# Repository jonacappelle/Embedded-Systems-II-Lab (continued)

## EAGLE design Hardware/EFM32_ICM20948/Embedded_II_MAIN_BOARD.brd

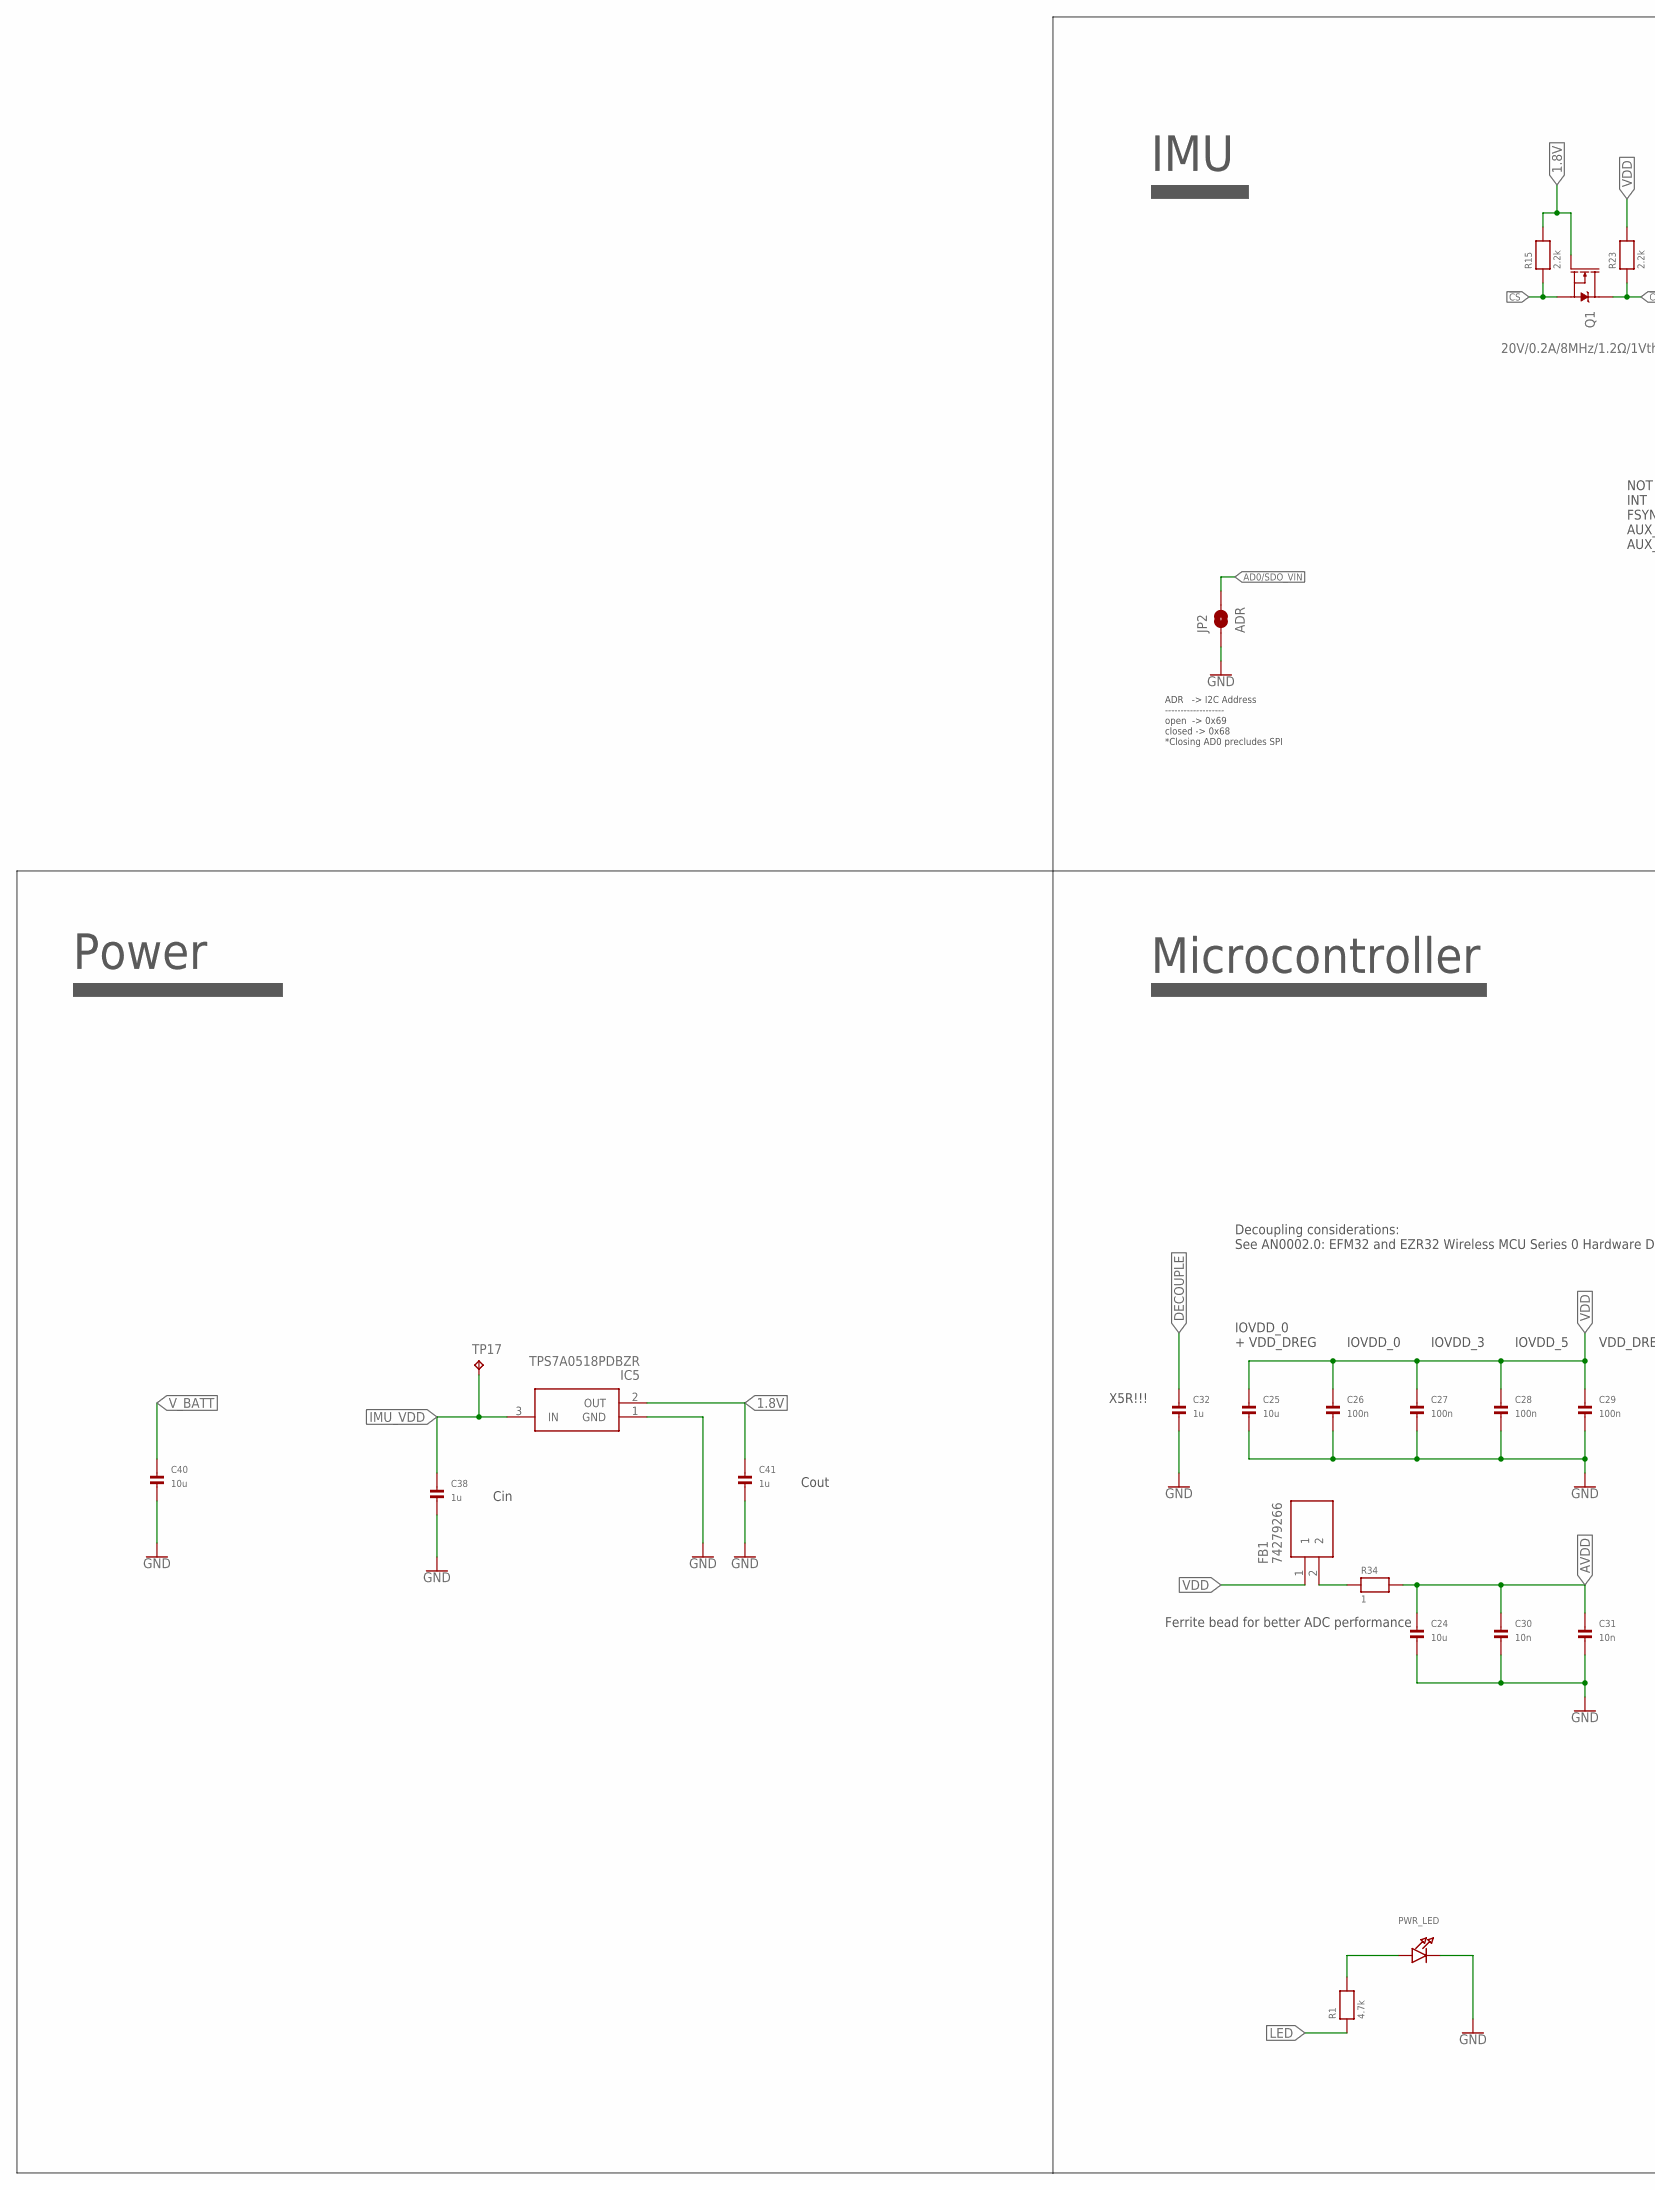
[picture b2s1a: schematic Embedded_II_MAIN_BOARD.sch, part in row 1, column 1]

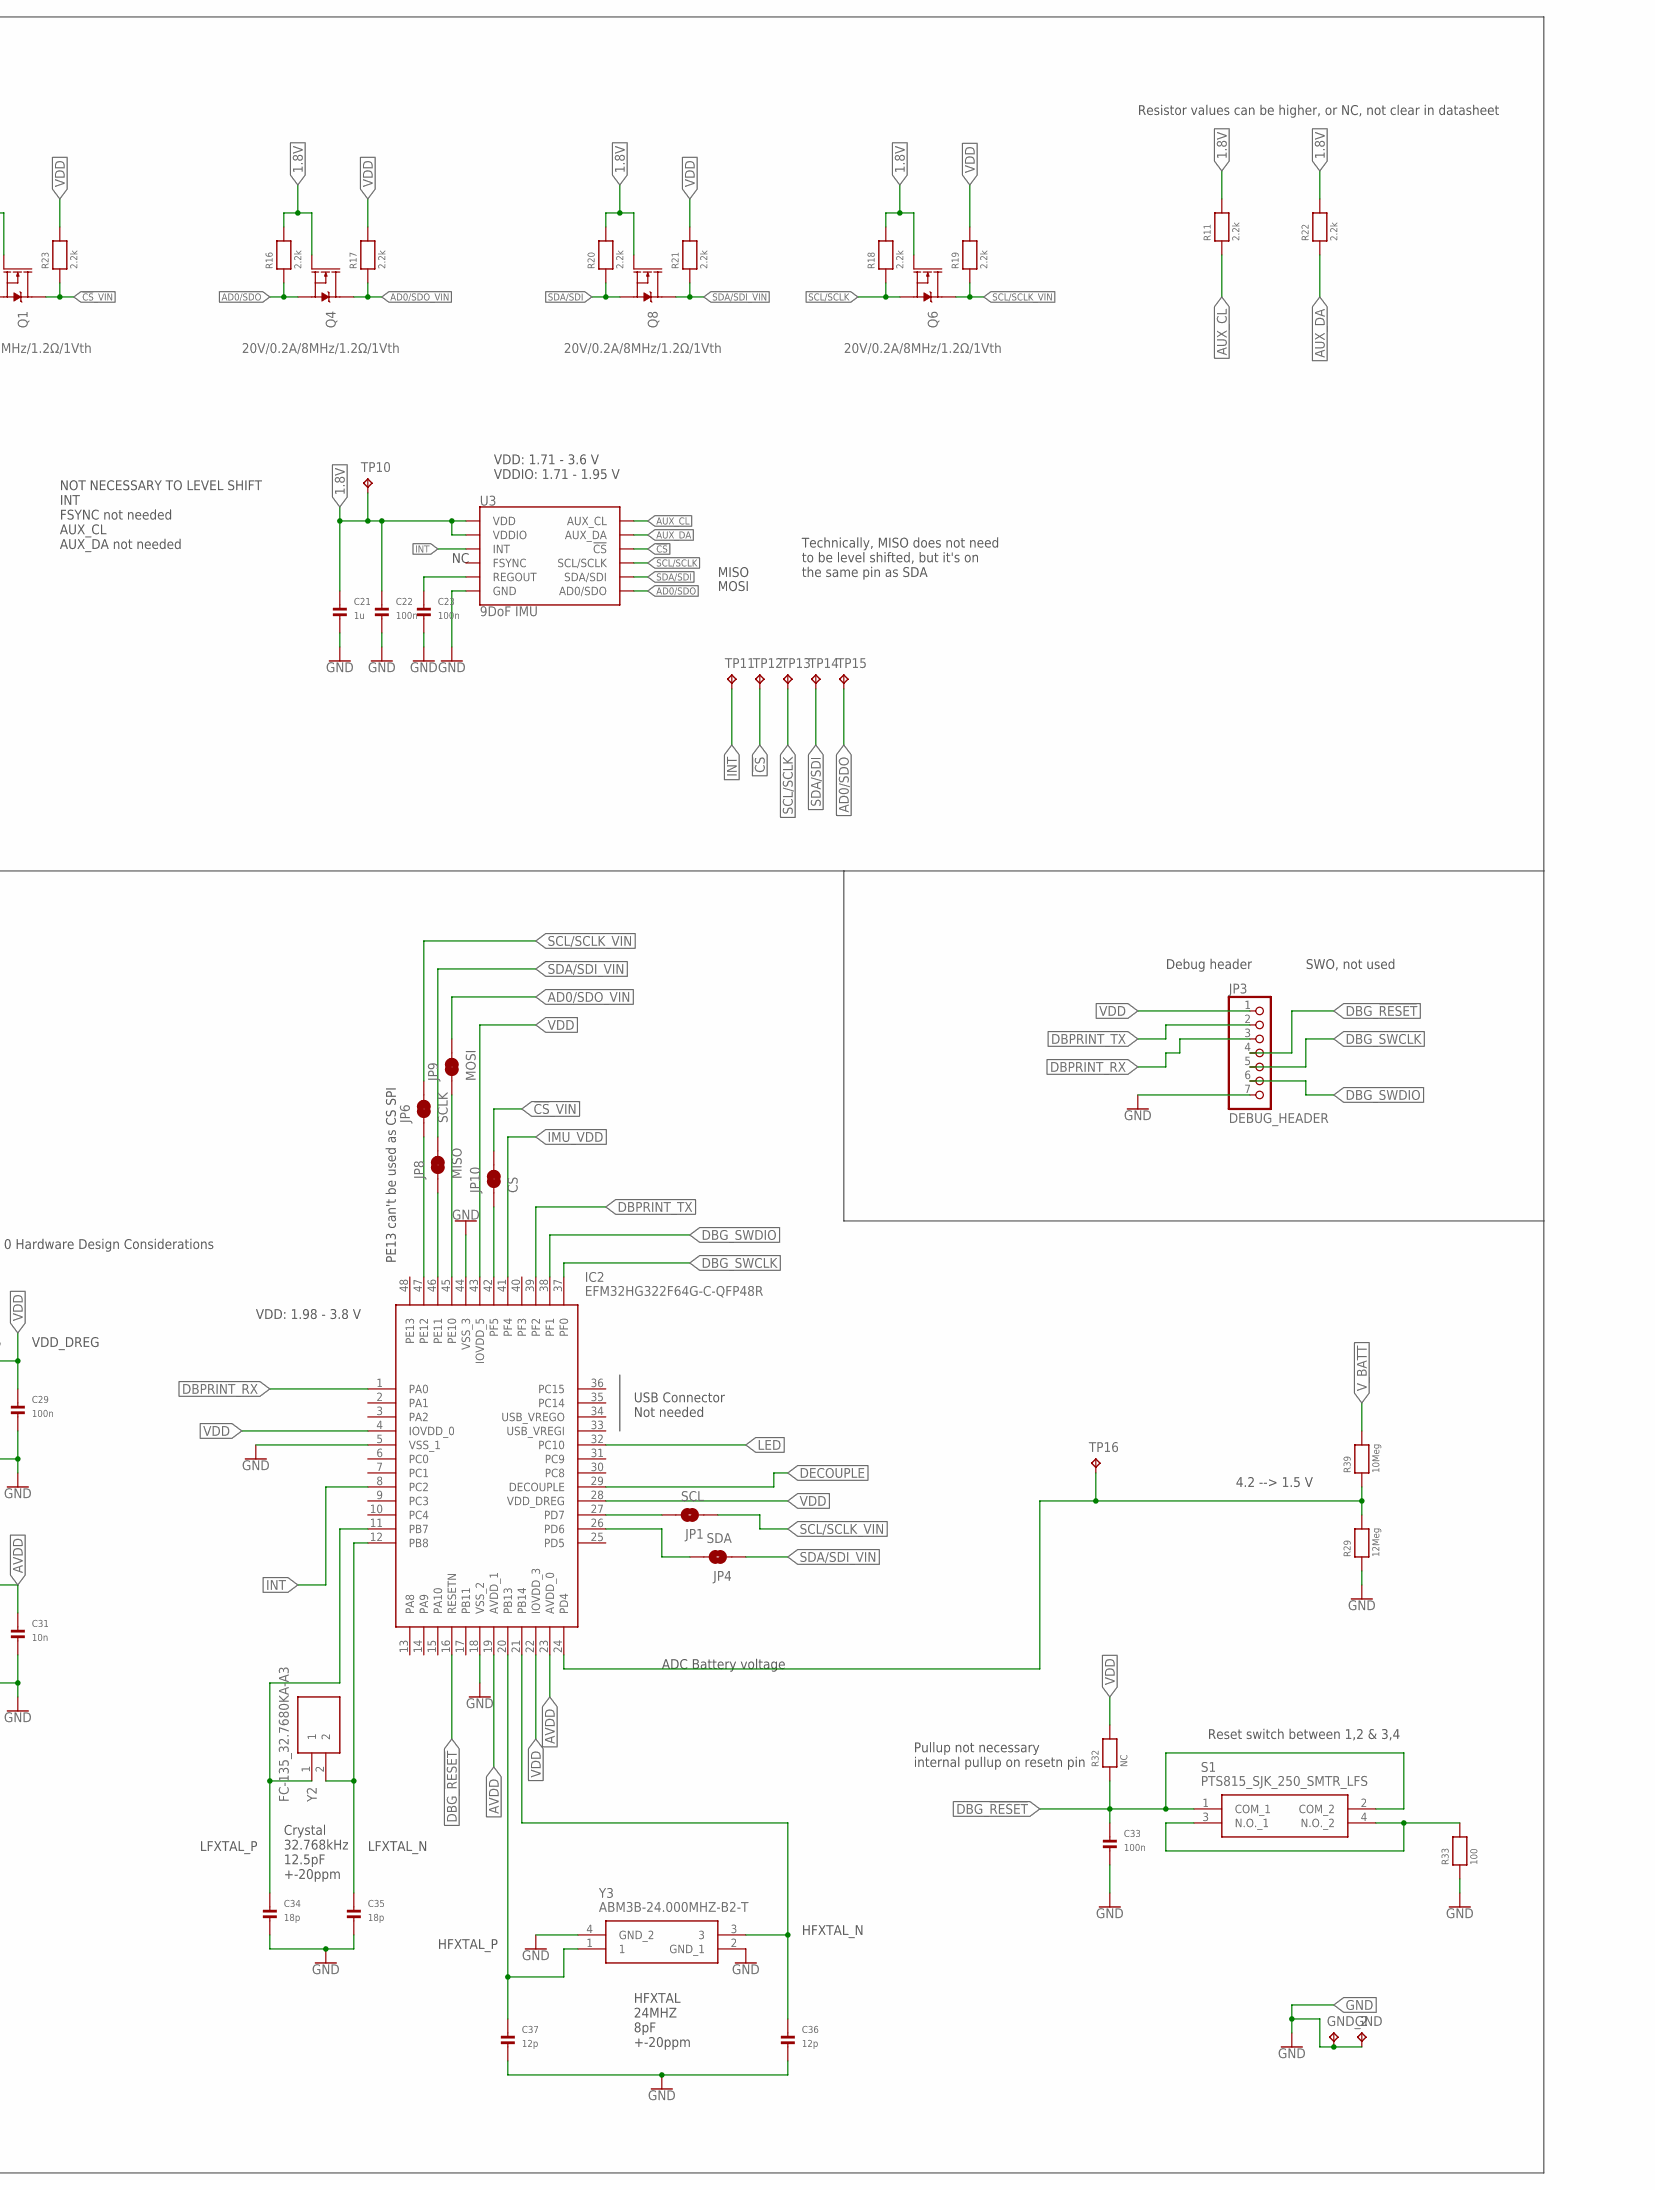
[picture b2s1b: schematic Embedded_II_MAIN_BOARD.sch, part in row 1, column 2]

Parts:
C21, C32, C38, C41: 1u; 0603
C22, C23, C26, C27, C28, C29, C33: 100n; 0603
C24, C25, C40: 10u; 0603
C30, C31: 10n; 0603
C34, C35: 18p; 0603
C36, C37: 12p; 0603
FB1: 74279266; BEADC1608X100N
GND: TPTP20SQ; TP20SQ
GND_2: TPTP20SQ; TP20SQ
IC2: EFM32HG322F64G-C-QFP48R; QFP50P900X900X120-48N
IC5: TPS7A0518PDBZR; SOT95P237X112-3N
JP1: SCL; SMT-JUMPER_2_NO_SILK
JP2: ADR; SMT-JUMPER_2_NO_SILK
JP3: DEBUG_HEADER; 1X07
JP4: SDA; SMT-JUMPER_2_NO_SILK
JP6: SCLK; SMT-JUMPER_2_NC_TRACE_SILK
JP8: MISO; SMT-JUMPER_2_NC_TRACE_SILK
JP9: MOSI; SMT-JUMPER_2_NC_TRACE_SILK
JP10: CS; SMT-JUMPER_2_NC_TRACE_SILK
PWR_LED: LED0805; CHIPLED_0805
Q1, Q4, Q6, Q8: 20V/0.2A/8MHz/1.2Ω/1Vth; SOT-416FL
R1: 4.7k; 0603
R11, R15, R16, R17, R18, R19, R20, R21, R22, R23: 2.2k; 0603
R29: 12Meg; 0603
R32: NC; 0603
R33: 100; 0603
R34: 1; 0603
R39: 10Meg; 0603
S1: PTS815_SJK_250_SMTR_LFS; PTS815SJK250SMTRLFS
TP10, TP11, TP12, TP13, TP14, TP15, TP16, TP17: TPTP10R; TP10R
U3: 9DoF IMU; SPARKFUN-SENSORS_QFN24-3X3
Y2: FC-135_32.7680KA-A3; FC135327680KAAG0
Y3: ABM3B-24.000MHZ-B2-T; ABM3B8000MHZ101UT

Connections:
1.8V: C21.1, C22.1, C41.1, IC5.2 (OUT), Q1.1 (G), Q4.1 (G), Q6.1 (G), Q8.1 (G), R11.2, R15.2, R16.2, R18.2, R20.2, R22.2, TP10.TP, U3.8 (VDDIO), U3.13 (VDD)
!CS: Q1.2 (S), R15.1, TP12.TP, U3.22 (!CS)
!CS!_VIN: JP10.2, Q1.3 (D), R23.1
AD0/SDO: Q4.2 (S), R16.1, TP15.TP, U3.9 (AD0/SDO)
AD0/SDO_VIN: JP2.2, JP9.2, Q4.3 (D), R17.1
AUX_CL: R11.1, U3.7 (AUX_CL)
AUX_DA: R22.1, U3.21 (AUX_DA)
AVDD: C24.1, C30.1, C31.1, IC2.19 (AVDD_1), IC2.23 (AVDD_0), R34.2
DBG_!RESET: C33.1, IC2.16 (RESETN), JP3.4, R32.1, S1.1 (COM_1), S1.2 (COM_2)
DBG_SWCLK: IC2.37 (PF0), JP3.5
DBG_SWDIO: IC2.38 (PF1), JP3.6
DBPRINT_RX: IC2.1 (PA0), JP3.3
DBPRINT_TX: IC2.39 (PF2), JP3.2
DECOUPLE: C32.1, IC2.29 (DECOUPLE)
GND: C21.2, C22.2, C23.2, C24.2, C25.2, C26.2, C27.2, C28.2, C29.2, C30.2, C31.2, C32.2, C33.2, C34.2, C35.2, C36.2, C37.2, C38.2, C40.2, C41.2, GND.TP, GND_2.TP, IC2.5 (VSS_1), IC2.18 (VSS_2), IC2.44 (VSS_3), IC5.1 (GND), JP2.1, JP3.7, PWR_LED.C, R29.1, R33.1, U3.18 (GND), U3.20 (GND), Y3.2 (GND_1), Y3.4 (GND_2)
IMU_VDD: C38.1, IC2.41 (PF4), IC5.3 (IN), TP17.TP
INT: IC2.8 (PC2), TP11.TP, U3.12 (INT)
LED: IC2.32 (PC10), R1.1
unnamed: IC2.27 (PD7), JP1.2
unnamed: PWR_LED.A, R1.2
unnamed: IC2.26 (PD6), JP4.2
unnamed: IC2.47 (PE12), JP6.1
unnamed: C35.1, IC2.12 (PB8), Y2.2
unnamed: C23.1, U3.10 (REGOUT)
unnamed: IC2.46 (PE11), JP8.1
unnamed: IC2.45 (PE10), JP9.1
unnamed: IC2.24 (PD4), R29.2, R39.1, TP16.TP
unnamed: C34.1, IC2.11 (PB7), Y2.1
unnamed: IC2.42 (PF5), JP10.1
unnamed: C37.1, IC2.20 (PB13), Y3.1
unnamed: C36.1, IC2.21 (PB14), Y3.3
unnamed: R33.2, S1.3 (N.O._1), S1.4 (N.O._2)
unnamed: FB1.2, R34.1
SCL/SCLK: Q6.2 (S), R18.1, TP13.TP, U3.23 (SCL/SCLK)
SCL/SCLK_VIN: JP1.1, JP6.2, Q6.3 (D), R19.1
SDA/SDI: Q8.2 (S), R20.1, TP14.TP, U3.24 (SDA/SDI)
SDA/SDI_VIN: JP4.1, JP8.2, Q8.3 (D), R21.1
VDD: C25.1, C26.1, C27.1, C28.1, C29.1, FB1.1, IC2.4 (IOVDD_0), IC2.22 (IOVDD_3), IC2.28 (VDD_DREG), IC2.43 (IOVDD_5), JP3.1, R17.2, R19.2, R21.2, R23.2, R32.2
V_BATT: C40.1, R39.2

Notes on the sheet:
IMU
Microcontroller
ADR -> I2C Address ------------------- open -> 0x69 closed -> 0x68 *Closing AD0 precludes SPI
VDD: 1.71 - 3.6 V VDDIO: 1.71 - 1.95 V
USB Connector Not needed
X5R!!!
Crystal 32.768kHz 12.5pF +-20ppm
HFXTAL 24MHZ 8pF +-20ppm
HFXTAL_P
HFXTAL_N
LFXTAL_P
LFXTAL_N
Reset switch between 1,2 & 3,4
Ferrite bead for better ADC performance
IOVDD_0 + VDD_DREG
IOVDD_0
IOVDD_3
IOVDD_5
Decoupling considerations: See AN0002.0: EFM32 and EZR32 Wireless MCU Series 0 Hardware Design Considerations
Pullup not necessary internal pullup on resetn pin
Debug header
Power
VDD: 1.98 - 3.8 V
Cin
Cout
PE13 can't be used as CS SPI
NOT NECESSARY TO LEVEL SHIFT INT FSYNC not needed AUX_CL AUX_DA not needed
MISO
MOSI
Technically, MISO does not need to be level shifted, but it's on the same pin as SDA
ADC Battery voltage
VDD_DREG
SWO, not used
Resistor values can be higher, or NC, not clear in datasheet
4.2 --> 1.5 V

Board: 2 copper layers, 66 parts (0 on the bottom side), 39 nets, no tracks yet.

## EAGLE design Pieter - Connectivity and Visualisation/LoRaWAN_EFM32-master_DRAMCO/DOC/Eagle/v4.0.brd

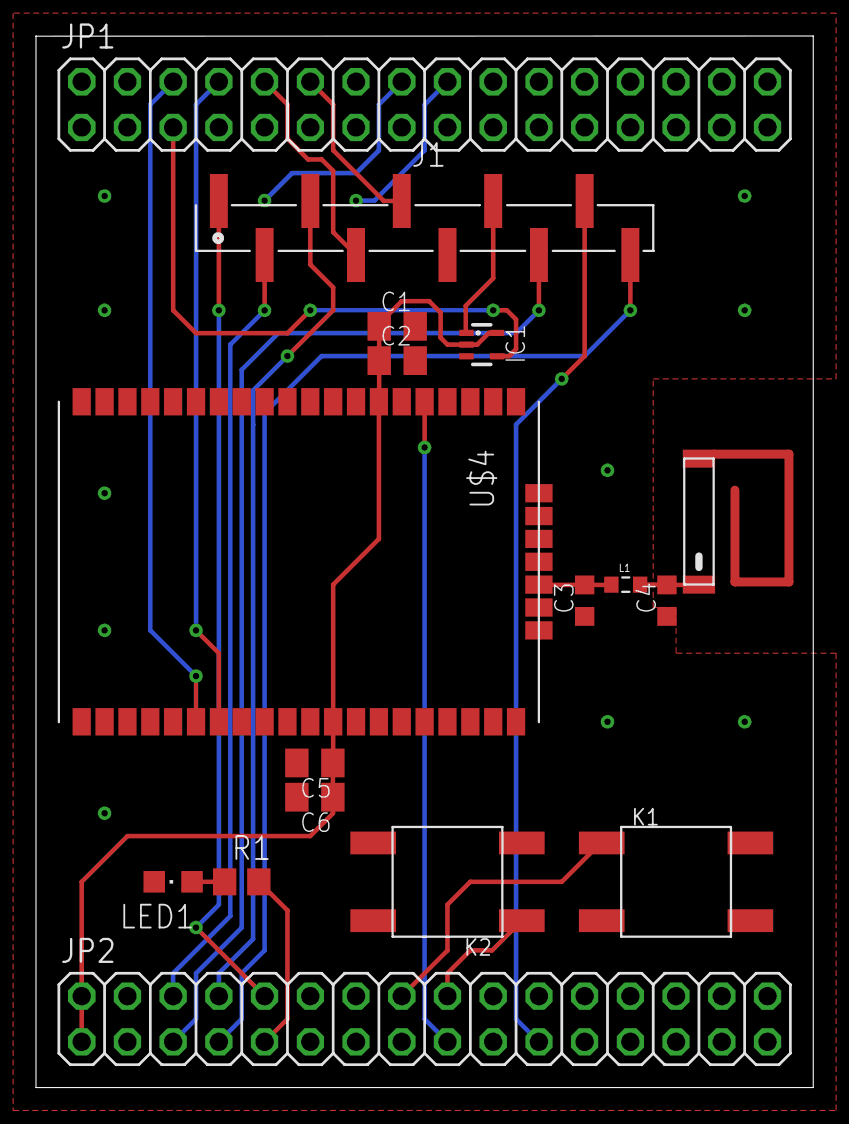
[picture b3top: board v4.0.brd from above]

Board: 2 copper layers, 43.2 x 58.4 mm, 17 parts (0 on the bottom side), 21 nets.

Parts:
C1, C5: 10u; C0805K
C2, C6: 100n; C0805K
C3, C4: C0603K
IC1: TS5A3166; SC70-5L
J1: 61001018321
JP1, JP2: 2X16
K1, K2: SW4-SMD-6.0X6.0X5.0MM
L1: WE-MK_0603_744786118; WE-MK_0603
LED1: CHIPLED_0805
R1: 820; R0805
U$2: ANTENNA868; CERAMIC-ANTENNA
U$4: RN2483

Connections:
GND: C1.2, C2.2, C3.1, C4.1, C5.2, C6.2, IC1.3, J1.6, JP1.3, JP1.4, JP1.29, JP1.30, JP2.3, JP2.4, JP2.29, JP2.30, K1.2, K2.2, LED1.C, U$4.GND, U$4.GND1, U$4.GND2, U$4.GND3, U$4.GND4, U$4.GND5, U$4.GND6, U$4.GND7, U$4.GND8, U$4.GND9, U$4.GND10, U$4.GND11, U$4.GND12
unnamed: LED1.A, R1.1
unnamed: C3.2, L1.1, U$4.RFH
unnamed: C4.2, L1.2, U$2.P$1
unnamed: IC1.1, J1.7
PA0: J1.8, JP2.5
PA1: J1.10, JP2.7
PA2: JP2.9, R1.2
PA10: JP2.17, U$4.RESET°
PB11: J1.9, JP2.21
PC0: J1.2, JP2.6
PC1: J1.3, JP2.8
PC2: J1.1, JP2.10
PC9: JP2.16, K1.1
PC10: JP2.18, K2.1
PD4: JP1.6, U$4.UART_TX
PD5: JP1.8, U$4.UART_RX
PD6: J1.4, JP1.10
PD7: J1.5, JP1.12
PF0: IC1.4, JP1.5
VMCU: C1.1, C2.1, C5.1, C6.1, IC1.2, IC1.5, JP2.1, JP2.2, U$4.VDD, U$4.VDD2

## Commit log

2020-03-27 Compass working (not tilt-compensated)
2020-03-27 Hardware main board v0.1
2020-03-27 pcb files + file pinnen
2020-03-27 start tekenen PCB
2020-03-29 schema getekend (bijna af), nog pcb routing
2020-03-30 schema getekend voeding_ bijna alle footprints volledig
2020-03-31 afgewerkte Energy Harvesting PCB
2020-04-01 main board pcb
2020-04-01 Routing main pcb
2020-04-01 main pcb lora update, bijna klaar
2020-04-01 renders voedings pcb
2020-04-02 finalisatie design main pcb (uC + imu + lora)
2020-04-03 PCB's DONE! :100:
2020-04-08 viasAangepast
2020-04-17 INFObestellingenzo
2020-04-17 update PCB + code + graphs
2020-04-17 update pcb + door te sturen info
2020-04-17 aanvulling niels
2020-04-17 schema toegevoegd
2020-04-18 embedded
2020-04-24 LoRa - Team Turn Table - Simplicity Studio Export
    Not the final version
    Sends student/emplyee number and players' score to The Things Network
2020-04-30 Verslag begin + ppt
2020-05-02 batturl
2020-05-02 Pieter - Player + Score (EFM32) -> Website
    EFM32 Lora (Player & Score) -> TTN Payload decoder -> Swagger API -> Mysql database -> Website
2020-05-02 Create Pieter - EFM32 -> Website
2020-05-02 Create 1
2020-05-02 Turntable Highscore Website
    Discription: Displays today's highscores, all time highscores and latest gameplays of Turntable Game Technologiecampus Gent from mysql database.
    Table items:
    *Medal for best 3 players
    *All time rank
    *Student/employee number
    *The player's scores
2020-05-02 The Things Network - Payload Decoder
    Decodes RAW bytes send trough LORA to playerId and playerScore in json format
2020-05-02 Swagger API data to Mysql database
    Python script with 1 minute execute interval to retreive data from temporary TTN database to permanent MYSQL database
2020-05-02 Send player Id and Score via RN2483 Lora on EFM32
    Silicon Labs Export
    *Encode playerId and playerScore to RAW bytes
    *Send bytes via RN2483 lora module
    *EFM32 Happy Gecko development board
2020-05-02 verslagDaan
2020-05-02 test
    test
2020-05-02 Connectivity and Visualisation
2020-05-03 Samenvoeging verslag Jona, Daan, Pieter
2020-05-05 Toevoeging deel Tuur
2020-05-06 adres wijziging
2020-05-06 verbeterd verslag
2020-05-06 code simon
2020-05-06 verslag
2020-05-06 Opmerkingen Tuur verbeterd, besluit nog schrijven!
    Alvast wat punten voor het besluit toegevoegd.
2020-05-07 Aangepaste verantwoordelijkheden
2020-05-07 besluit
2020-05-07 Verslag DONE!
2020-05-07 Opkuis + sorteren
2020-05-11 Eindpresentatie deel Pieter
2020-05-12 Aanpassingen pieter (korter)
2020-05-13 Eindpresentatie :100:
